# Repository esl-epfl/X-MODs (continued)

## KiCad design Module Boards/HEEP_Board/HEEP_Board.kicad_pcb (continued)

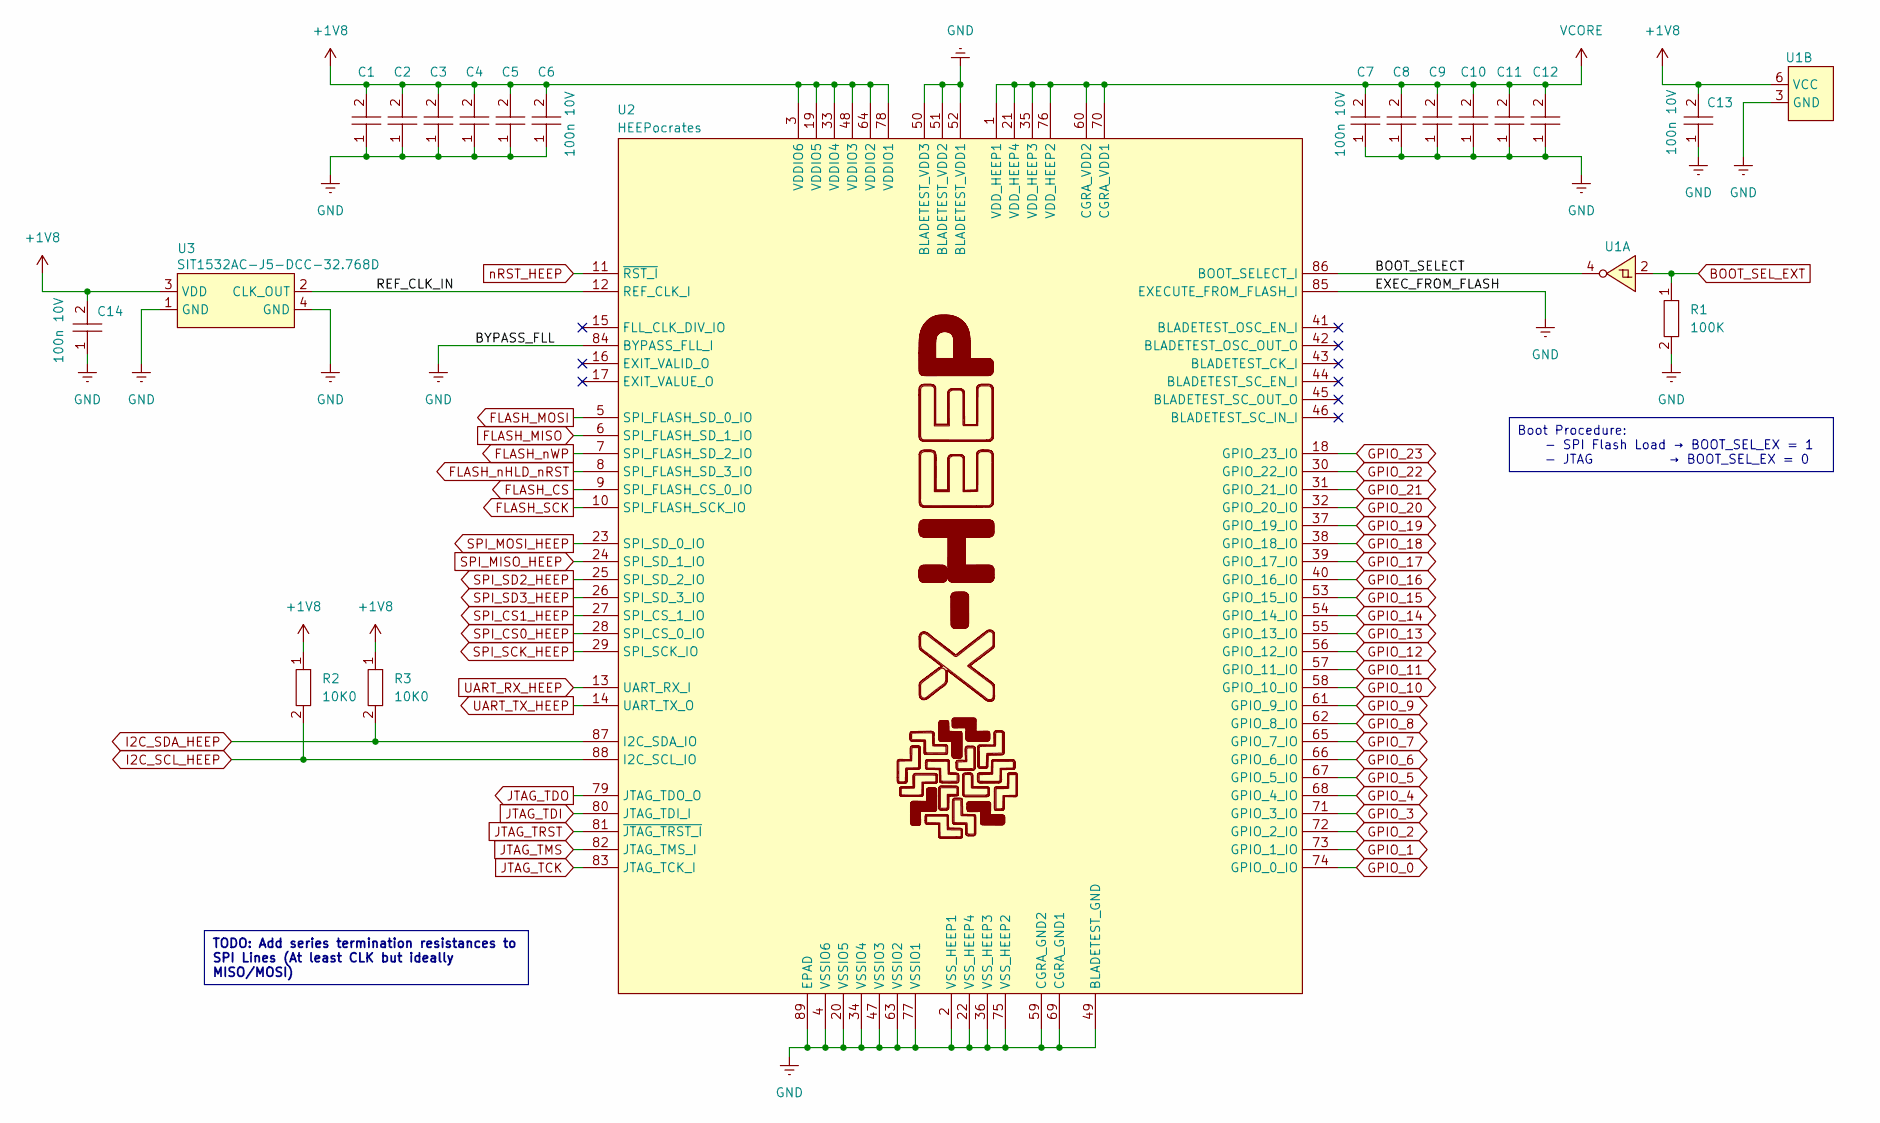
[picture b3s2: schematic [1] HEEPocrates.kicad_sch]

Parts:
C1, C2, C3, C4, C5, C6, C7, C8, C9, C10, C11, C12, C13, C14: 100n 10V; C0402
R1: 100K; R0402
R2, R3: 10K0; R0402
U1: X2SON-6
U2: HEEPocrates
U3: SIT1532AC-J5-DCC-32.768D; SIT1532AC

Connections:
+1V8: C1.2, C2.2, C3.2, C4.2, C5.2, C6.2, C13.2, C14.2, R2.1, R3.1, U1.6 (VCC), U2.3 (VDDIO6), U2.19 (VDDIO5), U2.33 (VDDIO4), U2.48 (VDDIO3), U2.64 (VDDIO2), U2.78 (VDDIO1), U3.3 (VDD); also elsewhere on the board
/[1] HEEPocrates/BOOT_SELECT: U1.4, U2.86 (BOOT_SELECT_I)
/[1] HEEPocrates/REF_CLK_IN: U2.12 (REF_CLK_I), U3.2 (CLK_OUT)
BOOT_SEL_EXT: R1.1, U1.2; also elsewhere on the board
FLASH_CS: U2.9 (SPI_FLASH_CS_0_IO); also elsewhere on the board
FLASH_MISO: U2.6 (SPI_FLASH_SD_1_IO); also elsewhere on the board
FLASH_MOSI: U2.5 (SPI_FLASH_SD_0_IO); also elsewhere on the board
FLASH_SCK: U2.10 (SPI_FLASH_SCK_IO); also elsewhere on the board
FLASH_nHLD_nRST: U2.8 (SPI_FLASH_SD_3_IO); also elsewhere on the board
FLASH_nWP: U2.7 (SPI_FLASH_SD_2_IO); also elsewhere on the board
GND: C1.1, C2.1, C3.1, C4.1, C5.1, C6.1, C7.1, C8.1, C9.1, C10.1, C11.1, C12.1, C13.1, C14.1, R1.2, U1.3 (GND), U2.2 (VSS_HEEP1), U2.4 (VSSIO6), U2.20 (VSSIO5), U2.22 (VSS_HEEP4), U2.34 (VSSIO4), U2.36 (VSS_HEEP3), U2.47 (VSSIO3), U2.49 (BLADETEST_GND), U2.50 (BLADETEST_VDD3), U2.51 (BLADETEST_VDD2), U2.52 (BLADETEST_VDD1), U2.59 (CGRA_GND2), U2.63 (VSSIO2), U2.69 (CGRA_GND1), U2.75 (VSS_HEEP2), U2.77 (VSSIO1), U2.84 (BYPASS_FLL_I), U2.85 (EXECUTE_FROM_FLASH_I), U2.89 (EPAD), U3.1 (GND), U3.4 (GND); also elsewhere on the board
GPIO_0: U2.74 (GPIO_0_IO); also elsewhere on the board
GPIO_1: U2.73 (GPIO_1_IO); also elsewhere on the board
GPIO_2: U2.72 (GPIO_2_IO); also elsewhere on the board
GPIO_3: U2.71 (GPIO_3_IO); also elsewhere on the board
GPIO_4: U2.68 (GPIO_4_IO); also elsewhere on the board
GPIO_5: U2.67 (GPIO_5_IO); also elsewhere on the board
GPIO_6: U2.66 (GPIO_6_IO); also elsewhere on the board
GPIO_7: U2.65 (GPIO_7_IO); also elsewhere on the board
GPIO_8: U2.62 (GPIO_8_IO); also elsewhere on the board
GPIO_9: U2.61 (GPIO_9_IO); also elsewhere on the board
GPIO_10: U2.58 (GPIO_10_IO); also elsewhere on the board
GPIO_11: U2.57 (GPIO_11_IO); also elsewhere on the board
GPIO_12: U2.56 (GPIO_12_IO); also elsewhere on the board
GPIO_13: U2.55 (GPIO_13_IO); also elsewhere on the board
GPIO_14: U2.54 (GPIO_14_IO); also elsewhere on the board
GPIO_15: U2.53 (GPIO_15_IO); also elsewhere on the board
GPIO_16: U2.40 (GPIO_16_IO); also elsewhere on the board
GPIO_17: U2.39 (GPIO_17_IO); also elsewhere on the board
GPIO_18: U2.38 (GPIO_18_IO); also elsewhere on the board
GPIO_19: U2.37 (GPIO_19_IO); also elsewhere on the board
GPIO_20: U2.32 (GPIO_20_IO); also elsewhere on the board
GPIO_21: U2.31 (GPIO_21_IO); also elsewhere on the board
GPIO_22: U2.30 (GPIO_22_IO); also elsewhere on the board
GPIO_23: U2.18 (GPIO_23_IO); also elsewhere on the board
I2C_SCL_HEEP: R2.2, U2.88 (I2C_SCL_IO); also elsewhere on the board
I2C_SDA_HEEP: R3.2, U2.87 (I2C_SDA_IO); also elsewhere on the board
JTAG_TCK: U2.83 (JTAG_TCK_I); also elsewhere on the board
JTAG_TDI: U2.80 (JTAG_TDI_I); also elsewhere on the board
JTAG_TDO: U2.79 (JTAG_TDO_O); also elsewhere on the board
JTAG_TMS: U2.82 (JTAG_TMS_I); also elsewhere on the board
JTAG_TRST: U2.81 (~JTAG_TRST_I); also elsewhere on the board
SPI_CS0_HEEP: U2.28 (SPI_CS_0_IO); also elsewhere on the board
SPI_CS1_HEEP: U2.27 (SPI_CS_1_IO); also elsewhere on the board
SPI_MISO_HEEP: U2.24 (SPI_SD_1_IO); also elsewhere on the board
SPI_MOSI_HEEP: U2.23 (SPI_SD_0_IO); also elsewhere on the board
SPI_SCK_HEEP: U2.29 (SPI_SCK_IO); also elsewhere on the board
SPI_SD2_HEEP: U2.25 (SPI_SD_2_IO); also elsewhere on the board
SPI_SD3_HEEP: U2.26 (SPI_SD_3_IO); also elsewhere on the board
UART_RX_HEEP: U2.13 (UART_RX_I); also elsewhere on the board
UART_TX_HEEP: U2.14 (UART_TX_O); also elsewhere on the board
VCORE: C7.2, C8.2, C9.2, C10.2, C11.2, C12.2, U2.1 (VDD_HEEP1), U2.21 (VDD_HEEP4), U2.35 (VDD_HEEP3), U2.60 (CGRA_VDD2), U2.70 (CGRA_VDD1), U2.76 (VDD_HEEP2); also elsewhere on the board
nRST_HEEP: U2.11 (~RST_I); also elsewhere on the board

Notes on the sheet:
Boot Procedure: - SPI Flash Load → BOOT_SEL_EX = 1 - JTAG → BOOT_SEL_EX = 0
TODO: Add series termination resistances to SPI Lines (At least CLK but ideally MISO/MOSI)

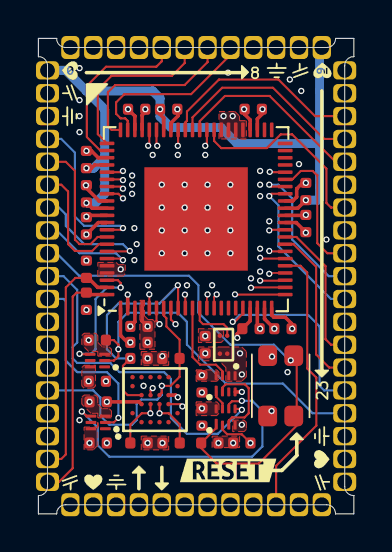
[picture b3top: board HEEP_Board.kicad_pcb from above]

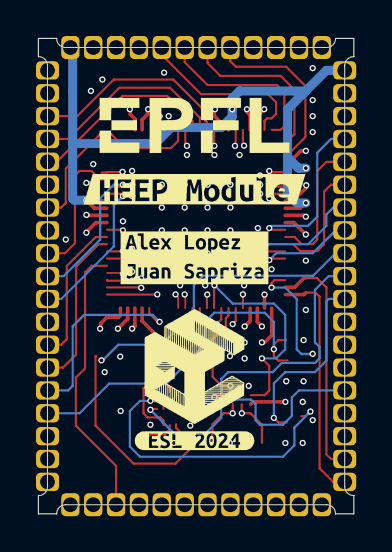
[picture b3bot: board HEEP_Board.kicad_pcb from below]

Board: 6 copper layers, 17.5 x 26.4 mm, 40 parts (3 on the bottom side), 59 nets.

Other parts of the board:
kibuzzard-66E1D769: G***; kibuzzard-66E1D769
kibuzzard-66E06A67: G***; kibuzzard-66E06A67
kibuzzard-66E06AA7: G***; kibuzzard-66E06AA7
kibuzzard-66E06AC0: G***; kibuzzard-66E06AC0

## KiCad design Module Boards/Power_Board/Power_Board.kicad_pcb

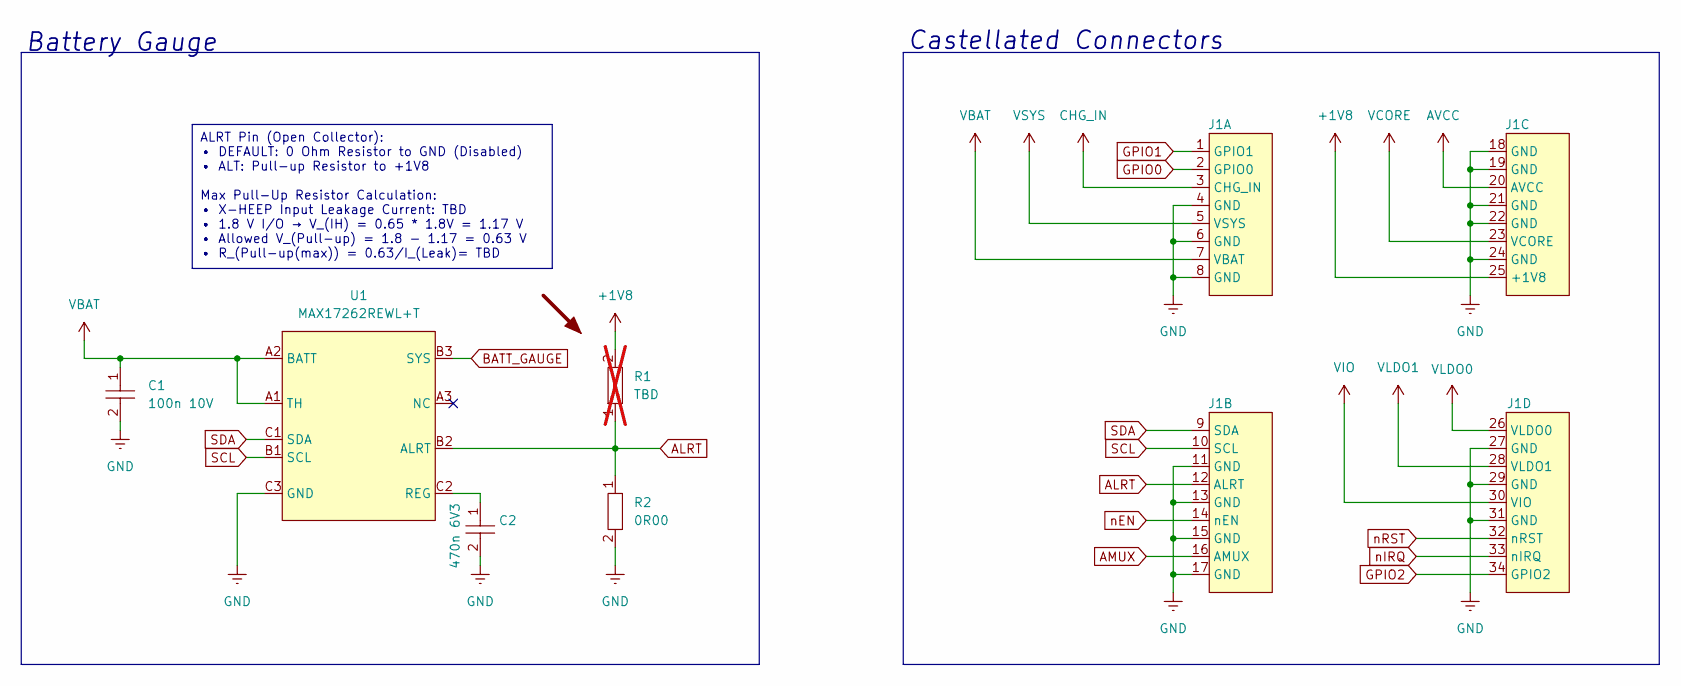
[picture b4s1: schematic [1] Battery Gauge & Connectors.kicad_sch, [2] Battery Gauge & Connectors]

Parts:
C1: 100n 10V; C0402
C2: 470n 6V3; C0402
J1: Power_Board_Castellated_Conn_1.27mm
R1: TBD; R0402; not fitted
R2: 0R00; R0402
U1: MAX17262REWL+T; WLCSP-9_1.468x1.448mm_P0.4mm

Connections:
+1V8: J1.25 (+1V8), R1.2; also elsewhere on the board
ALRT: J1.12 (ALRT), R1.1, R2.1, U1.B2 (ALRT)
AMUX: J1.16 (AMUX); also elsewhere on the board
AVCC: J1.20 (AVCC); also elsewhere on the board
BATT_GAUGE: U1.B3 (SYS); also elsewhere on the board
CHG_IN: J1.3 (CHG_IN); also elsewhere on the board
GND: C1.2, C2.2, J1.4 (GND), J1.6 (GND), J1.8 (GND), J1.11 (GND), J1.13 (GND), J1.15 (GND), J1.17 (GND), J1.18 (GND), J1.19 (GND), J1.21 (GND), J1.22 (GND), J1.24 (GND), J1.27 (GND), J1.29 (GND), J1.31 (GND), R2.2, U1.C3 (GND); also elsewhere on the board
GPIO0: J1.2 (GPIO0); also elsewhere on the board
GPIO1: J1.1 (GPIO1); also elsewhere on the board
GPIO2: J1.34 (GPIO2); also elsewhere on the board
unnamed: C2.1, U1.C2 (REG)
SCL: J1.10 (SCL), U1.B1 (SCL); also elsewhere on the board
SDA: J1.9 (SDA), U1.C1 (SDA); also elsewhere on the board
VBAT: C1.1, J1.7 (VBAT), U1.A1 (TH), U1.A2 (BATT)
VCORE: J1.23 (VCORE); also elsewhere on the board
VIO: J1.30 (VIO); also elsewhere on the board
VLDO0: J1.26 (VLDO0); also elsewhere on the board
VLDO1: J1.28 (VLDO1); also elsewhere on the board
VSYS: J1.5 (VSYS); also elsewhere on the board
nEN: J1.14 (nEN); also elsewhere on the board
nIRQ: J1.33 (nIRQ); also elsewhere on the board
nRST: J1.32 (nRST); also elsewhere on the board

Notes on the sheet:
ALRT Pin (Open Collector): • DEFAULT: 0 Ohm Resistor to GND (Disabled) • ALT: Pull-up Resistor to +1V8 Max Pull-Up Resistor Calculation: • X-HEEP Input Leakage Current: TBD • 1.8 V I/O → V_(IH) = 0.65 * 1.8V = 1.17 V • Allowed V_(Pull-up) = 1.8 - 1.17 = 0.63 V • R_(Pull-up(max)) = 0.63/I_(Leak)= TBD
Battery Gauge
Castellated Connectors

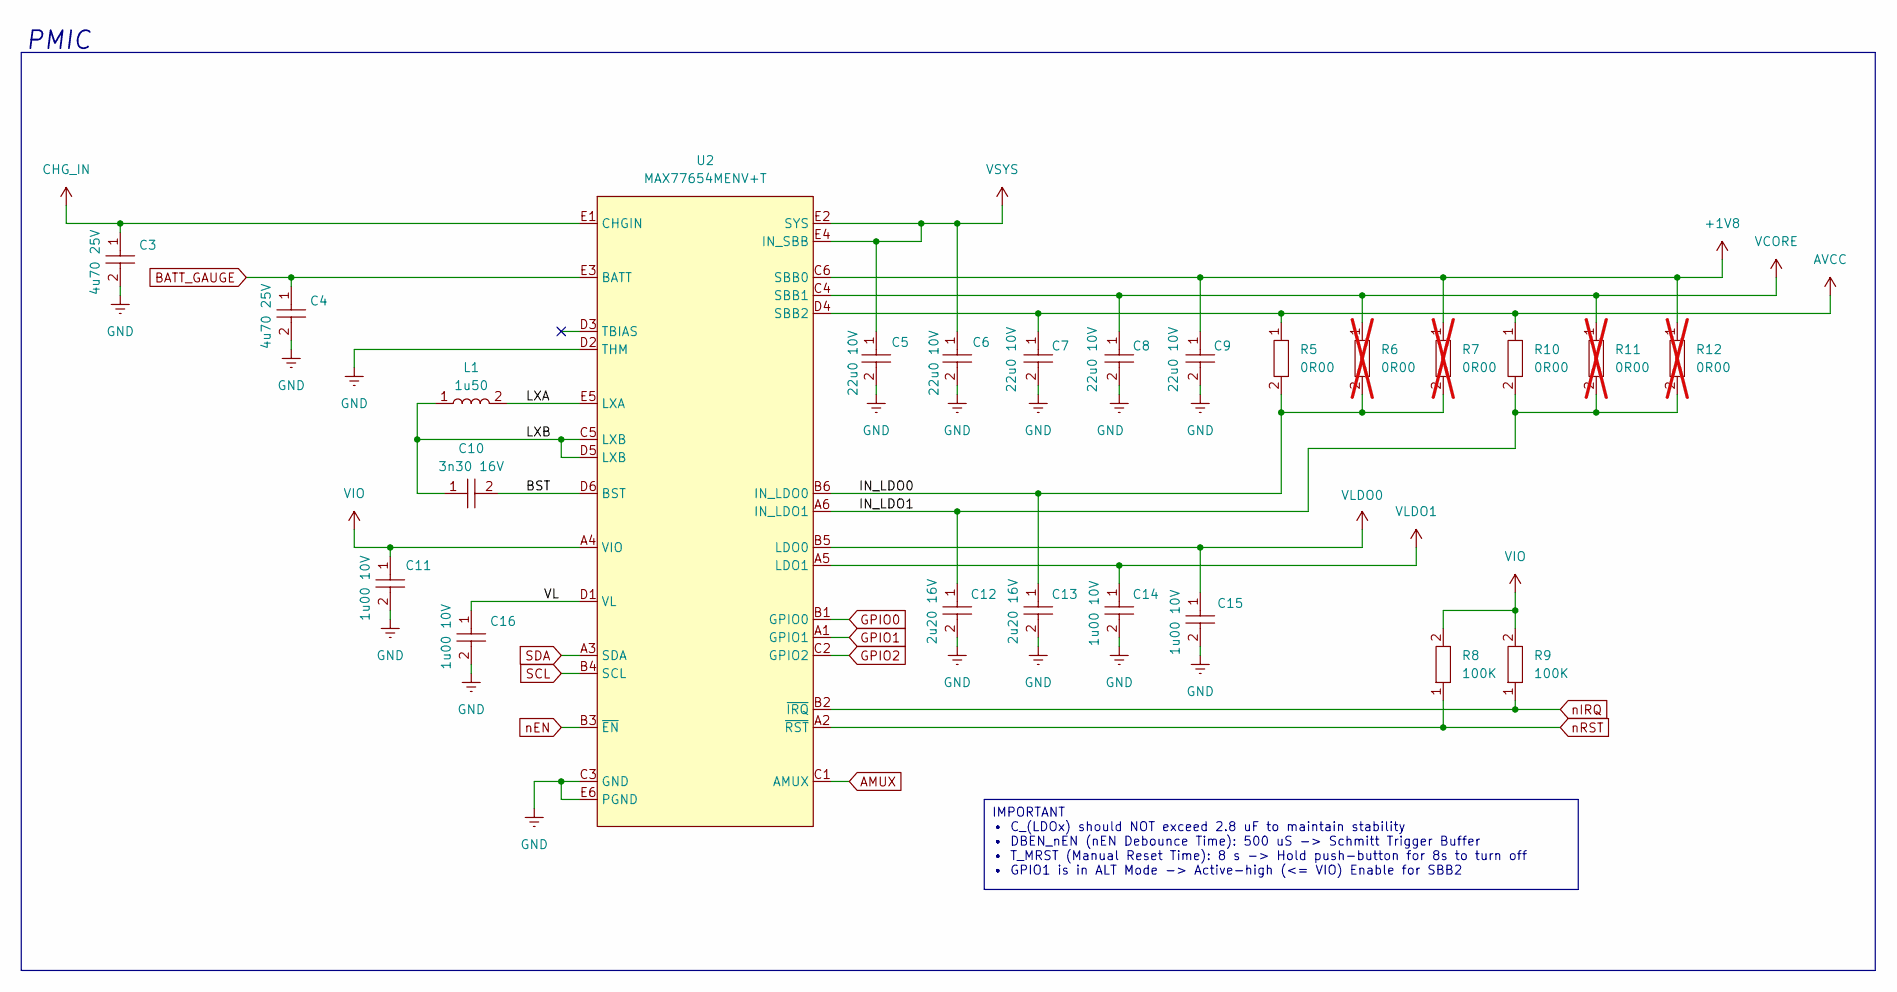
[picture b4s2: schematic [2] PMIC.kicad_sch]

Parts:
C3, C4: 4u70 25V; C0603
C5, C6, C7, C8, C9: 22u0 10V; C0603
C10: 3n30 16V; C0402
C11, C14, C15, C16: 1u00 10V; C0402
C12, C13: 2u20 16V; C0402
L1: 1u50; L0806
R5, R10: 0R00; R0402
R6, R7, R11, R12: 0R00; R0402; not fitted
R8, R9: 100K; R0402
U2: MAX77654MENV+T; WLCSP-30_2.788x2.338mm_P0.4mm

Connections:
+1V8: C9.1, R7.1, R12.1, U2.C6 (SBB0); also elsewhere on the board
/[2] PMIC/BST: C10.2, U2.D6 (BST)
/[2] PMIC/IN_LDO0: C13.1, R5.2, R6.2, R7.2, U2.B6 (IN_LDO0)
/[2] PMIC/IN_LDO1: C12.1, R10.2, R11.2, R12.2, U2.A6 (IN_LDO1)
/[2] PMIC/LXA: L1.2, U2.E5 (LXA)
/[2] PMIC/LXB: C10.1, L1.1, U2.C5 (LXB), U2.D5 (LXB)
/[2] PMIC/VL: C16.1, U2.D1 (VL)
AMUX: U2.C1 (AMUX); also elsewhere on the board
AVCC: C7.1, R5.1, R10.1, U2.D4 (SBB2); also elsewhere on the board
BATT_GAUGE: C4.1, U2.E3 (BATT); also elsewhere on the board
CHG_IN: C3.1, U2.E1 (CHGIN); also elsewhere on the board
GND: C3.2, C4.2, C5.2, C6.2, C7.2, C8.2, C9.2, C11.2, C12.2, C13.2, C14.2, C15.2, C16.2, U2.C3 (GND), U2.D2 (THM), U2.E6 (PGND); also elsewhere on the board
GPIO0: U2.B1 (GPIO0); also elsewhere on the board
GPIO1: U2.A1 (GPIO1); also elsewhere on the board
GPIO2: U2.C2 (GPIO2); also elsewhere on the board
SCL: U2.B4 (SCL); also elsewhere on the board
SDA: U2.A3 (SDA); also elsewhere on the board
VCORE: C8.1, R6.1, R11.1, U2.C4 (SBB1); also elsewhere on the board
VIO: C11.1, R8.2, R9.2, U2.A4 (VIO); also elsewhere on the board
VLDO0: C15.1, U2.B5 (LDO0); also elsewhere on the board
VLDO1: C14.1, U2.A5 (LDO1); also elsewhere on the board
VSYS: C5.1, C6.1, U2.E2 (SYS), U2.E4 (IN_SBB); also elsewhere on the board
nEN: U2.B3 (~EN); also elsewhere on the board
nIRQ: R9.1, U2.B2 (~IRQ); also elsewhere on the board
nRST: R8.1, U2.A2 (~RST); also elsewhere on the board

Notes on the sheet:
IMPORTANT • C_(LDOx) should NOT exceed 2.8 uF to maintain stability • DBEN_nEN (nEN Debounce Time): 500 uS -> Schmitt Trigger Buffer • T_MRST (Manual Reset Time): 8 s -> Hold push-button for 8s to turn off • GPIO1 is in ALT Mode -> Active-high (<= VIO) Enable for SBB2
PMIC

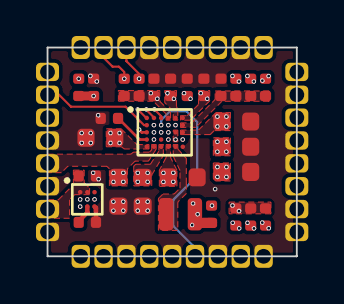
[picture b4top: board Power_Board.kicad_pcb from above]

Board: 6 copper layers, 13.8 x 11.6 mm, 30 parts (0 on the bottom side), 28 nets.

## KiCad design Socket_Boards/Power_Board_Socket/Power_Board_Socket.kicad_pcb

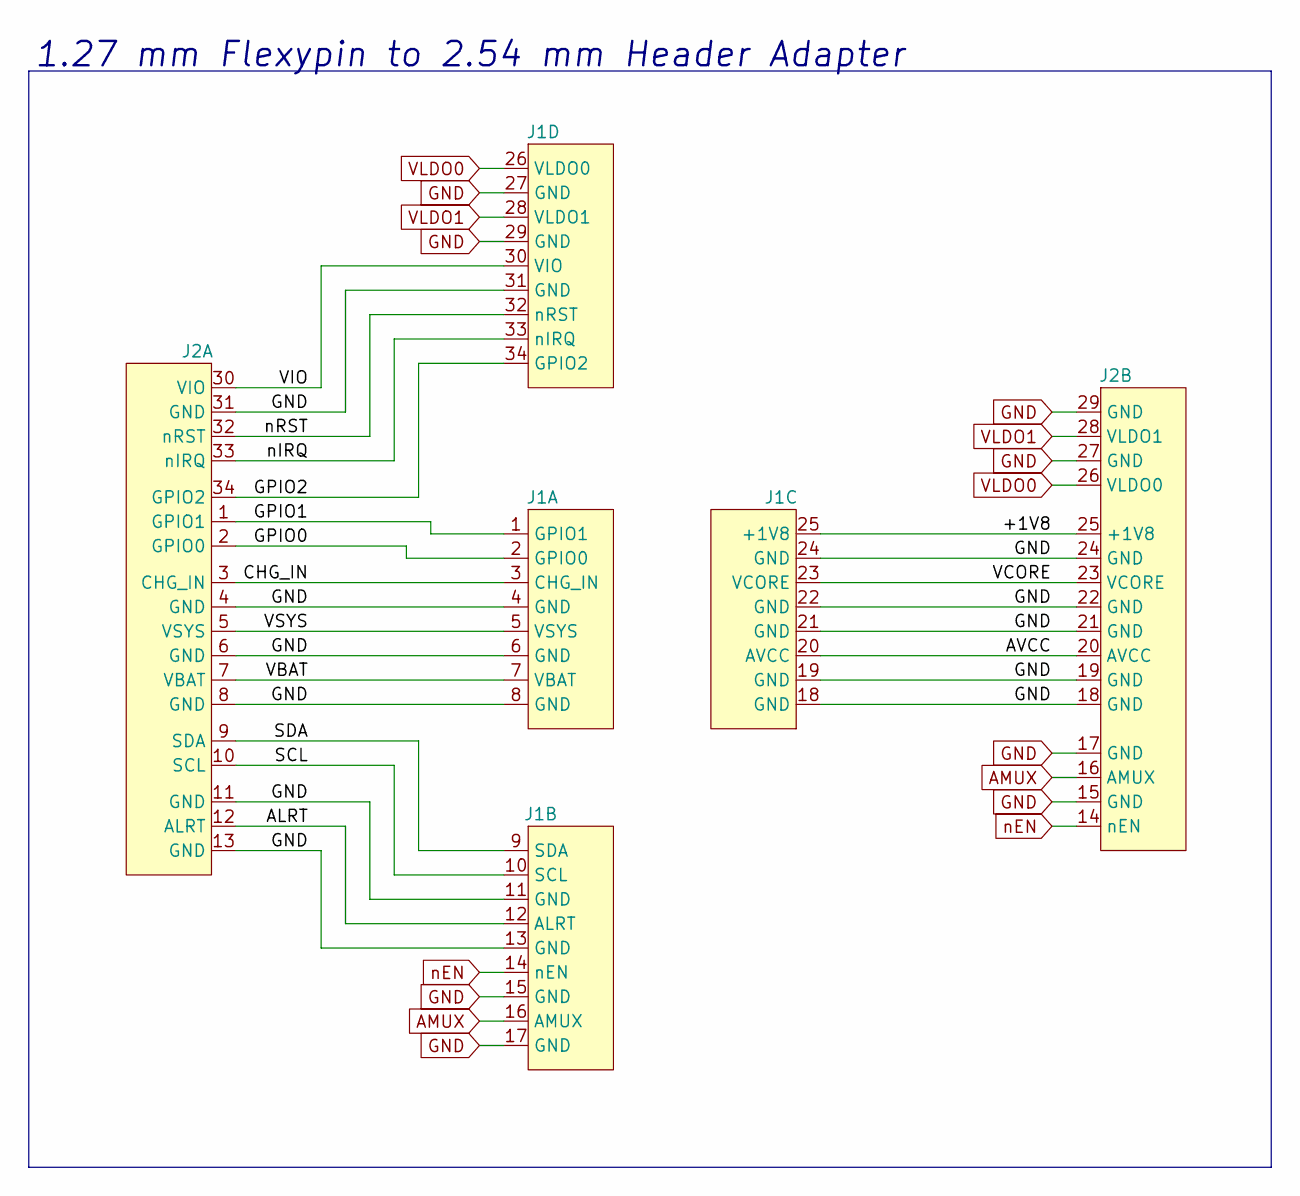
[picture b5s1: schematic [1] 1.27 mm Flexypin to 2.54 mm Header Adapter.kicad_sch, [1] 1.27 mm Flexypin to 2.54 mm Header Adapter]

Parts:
J1: Power_Board_Socket_Conn_1.27mm
J2: Power_Board_Header_Conn_2.54mm

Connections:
/[1] 1.27 mm Flexypin to 2.54 mm Header Adapter/+1V8: J1.25 (+1V8), J2.25 (+1V8)
/[1] 1.27 mm Flexypin to 2.54 mm Header Adapter/ALRT: J1.12 (ALRT), J2.12 (ALRT)
/[1] 1.27 mm Flexypin to 2.54 mm Header Adapter/AVCC: J1.20 (AVCC), J2.20 (AVCC)
/[1] 1.27 mm Flexypin to 2.54 mm Header Adapter/CHG_IN: J1.3 (CHG_IN), J2.3 (CHG_IN)
/[1] 1.27 mm Flexypin to 2.54 mm Header Adapter/GPIO0: J1.2 (GPIO0), J2.2 (GPIO0)
/[1] 1.27 mm Flexypin to 2.54 mm Header Adapter/GPIO1: J1.1 (GPIO1), J2.1 (GPIO1)
/[1] 1.27 mm Flexypin to 2.54 mm Header Adapter/GPIO2: J1.34 (GPIO2), J2.34 (GPIO2)
/[1] 1.27 mm Flexypin to 2.54 mm Header Adapter/SCL: J1.10 (SCL), J2.10 (SCL)
/[1] 1.27 mm Flexypin to 2.54 mm Header Adapter/SDA: J1.9 (SDA), J2.9 (SDA)
/[1] 1.27 mm Flexypin to 2.54 mm Header Adapter/VBAT: J1.7 (VBAT), J2.7 (VBAT)
/[1] 1.27 mm Flexypin to 2.54 mm Header Adapter/VCORE: J1.23 (VCORE), J2.23 (VCORE)
/[1] 1.27 mm Flexypin to 2.54 mm Header Adapter/VIO: J1.30 (VIO), J2.30 (VIO)
/[1] 1.27 mm Flexypin to 2.54 mm Header Adapter/VSYS: J1.5 (VSYS), J2.5 (VSYS)
/[1] 1.27 mm Flexypin to 2.54 mm Header Adapter/nIRQ: J1.33 (nIRQ), J2.33 (nIRQ)
/[1] 1.27 mm Flexypin to 2.54 mm Header Adapter/nRST: J1.32 (nRST), J2.32 (nRST)
AMUX: J1.16 (AMUX), J2.16 (AMUX)
GND: J1.4 (GND), J1.6 (GND), J1.8 (GND), J1.11 (GND), J1.13 (GND), J1.15 (GND), J1.17 (GND), J1.18 (GND), J1.19 (GND), J1.21 (GND), J1.22 (GND), J1.24 (GND), J1.27 (GND), J1.29 (GND), J1.31 (GND), J2.4 (GND), J2.6 (GND), J2.8 (GND), J2.11 (GND), J2.13 (GND), J2.15 (GND), J2.17 (GND), J2.18 (GND), J2.19 (GND), J2.21 (GND), J2.22 (GND), J2.24 (GND), J2.27 (GND), J2.29 (GND), J2.31 (GND)
VLDO0: J1.26 (VLDO0), J2.26 (VLDO0)
VLDO1: J1.28 (VLDO1), J2.28 (VLDO1)
nEN: J1.14 (nEN), J2.14 (nEN)

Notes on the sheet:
1.27 mm Flexypin to 2.54 mm Header Adapter

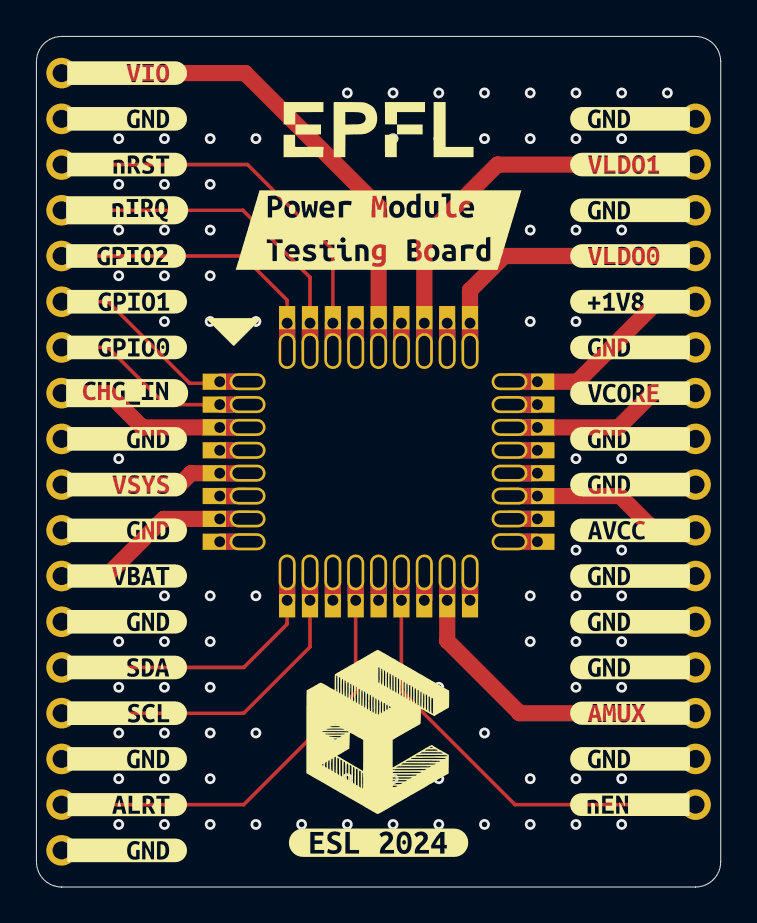
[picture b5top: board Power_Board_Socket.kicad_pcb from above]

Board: 4 copper layers, 38.0 x 47.3 mm, 39 parts (1 on the bottom side), 20 nets.

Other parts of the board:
kibuzzard-66CF9CA5: G***; kibuzzard-66CF9CA5
kibuzzard-66CF9CAA: G***; kibuzzard-66CF9CAA
kibuzzard-66CF9CC6: G***; kibuzzard-66CF9CC6
kibuzzard-66CF9CD9: G***; kibuzzard-66CF9CD9
kibuzzard-66CF9CE3: G***; kibuzzard-66CF9CE3
kibuzzard-66CF9CE9: G***; kibuzzard-66CF9CE9
kibuzzard-66CF9CF0: G***; kibuzzard-66CF9CF0
kibuzzard-66CF9CF8: G***; kibuzzard-66CF9CF8
kibuzzard-66CF9CFE: G***; kibuzzard-66CF9CFE
kibuzzard-66CF9D0A: G***; kibuzzard-66CF9D0A
kibuzzard-66CF9D2A: G***; kibuzzard-66CF9D2A
kibuzzard-66CF9D04: G***; kibuzzard-66CF9D04
kibuzzard-66CF9D5F, kibuzzard-66CF9D5F#2, kibuzzard-66CF9D5F#3, kibuzzard-66CF9D5F#4, kibuzzard-66CF9D5F#5, kibuzzard-66CF9D5F#6, kibuzzard-66CF9D5F#7, kibuzzard-66CF9D5F#8, kibuzzard-66CF9D5F#9: G***; kibuzzard-66CF9D5F
kibuzzard-66CF9D8B: G***; kibuzzard-66CF9D8B
kibuzzard-66CF9D9B: G***; kibuzzard-66CF9D9B
kibuzzard-66CF9D14: G***; kibuzzard-66CF9D14
kibuzzard-66CF9D25: G***; kibuzzard-66CF9D25
kibuzzard-66CF9D65: G***; kibuzzard-66CF9D65
kibuzzard-66CF9D91: G***; kibuzzard-66CF9D91
kibuzzard-66CF9DA2: G***; kibuzzard-66CF9DA2
kibuzzard-66CF9DA9: G***; kibuzzard-66CF9DA9
kibuzzard-66CF9DAF: G***; kibuzzard-66CF9DAF
kibuzzard-66CFAA7E: G***; kibuzzard-66CFAA7E
kibuzzard-66CFAA8B: G***; kibuzzard-66CFAA8B
kibuzzard-66CFAA85: G***; kibuzzard-66CFAA85
kibuzzard-66CFC1A0: G***; kibuzzard-66CFC1A0
kibuzzard-66CFC30E: G***; kibuzzard-66CFC30E
kibuzzard-66CFCF0D: G***; kibuzzard-66CFCF0D
kibuzzard-67530430: G***; kibuzzard-67530430
